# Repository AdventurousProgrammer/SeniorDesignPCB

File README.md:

# SeniorDesignPCB
This is the Diwali Light Chaser PCB For Senior Design

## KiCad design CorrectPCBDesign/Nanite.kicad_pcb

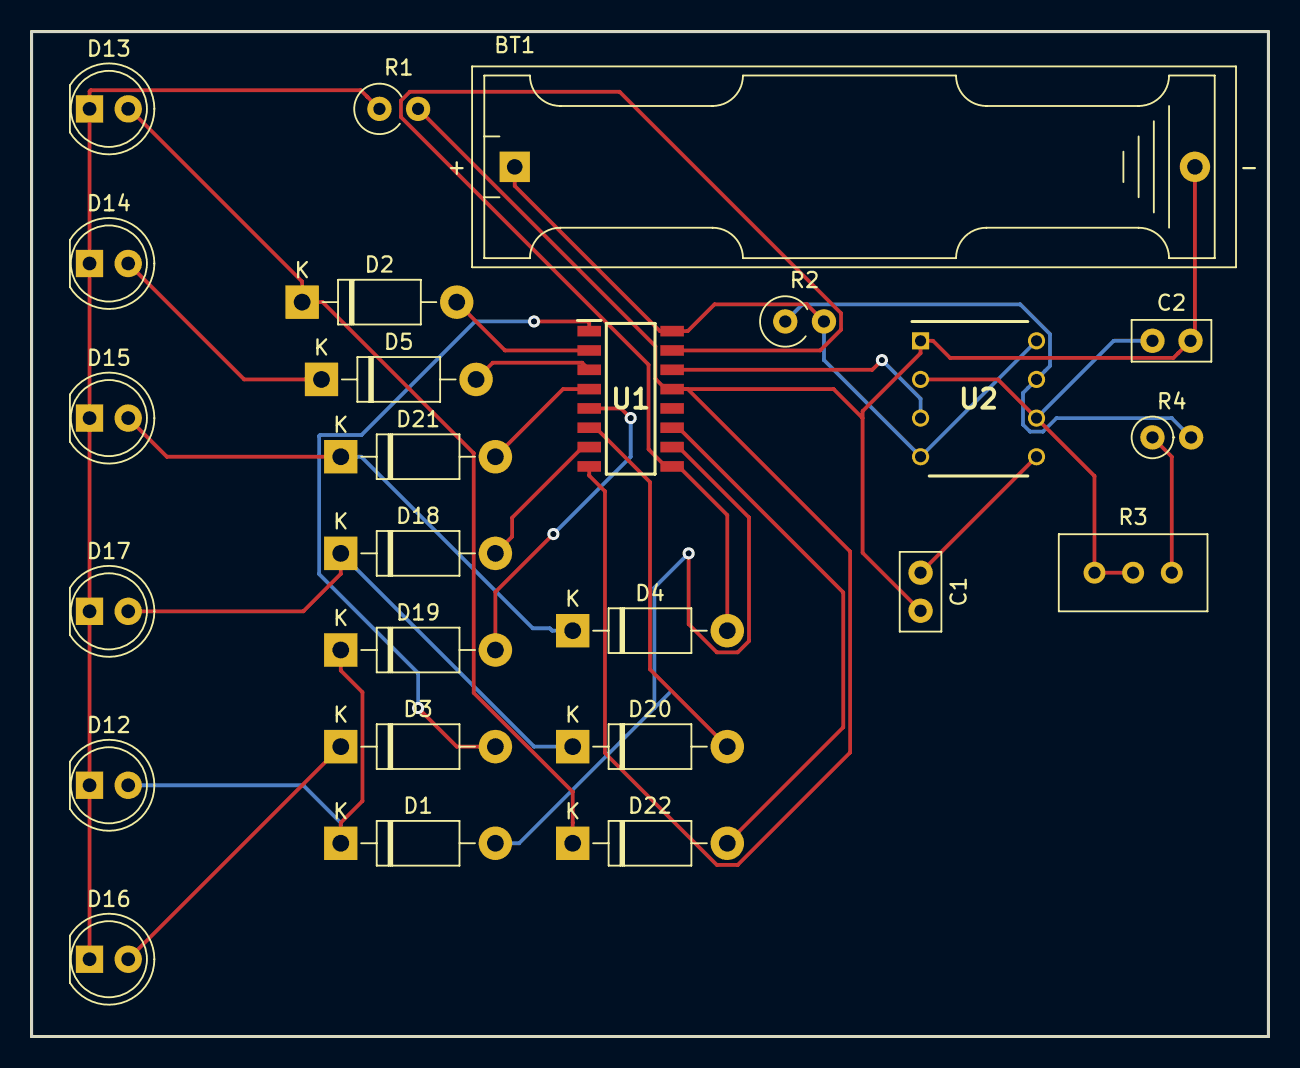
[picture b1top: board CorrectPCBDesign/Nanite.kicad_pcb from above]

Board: 2 copper layers, 81.3 x 66.0 mm, 25 parts (0 on the bottom side), 24 nets.

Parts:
BT1: Battery_Cell; BatteryHolder_Keystone_2466_1xAAA
C1: 1 nF; C_Disc_D5.0mm_W2.5mm_P2.50mm
C2: 4.7 uF; C_Disc_D5.0mm_W2.5mm_P2.50mm
D1, D2, D3, D4, D5, D18, D19, D20, D21, D22: 1N4007; D_DO-41_SOD81_P10.16mm_Horizontal
D12, D13, D14, D15, D16, D17: LED; LED_D5.0mm
R1: 1k; R_Axial_DIN0309_L9.0mm_D3.2mm_P2.54mm_Vertical
R2: 4.7k; R_Axial_DIN0309_L9.0mm_D3.2mm_P2.54mm_Vertical
R3: 1k; Potentiometer_Bourns_3296W_Vertical
R4: 100k; R_Axial_DIN0207_L6.3mm_D2.5mm_P2.54mm_Vertical
U1: 4017; SOIC127P600X175-16N
U2: TLC555; DIP762W53P254L980H533Q8N

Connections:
GNDA: BT1.2, C1.2, C2.2, R1.2, U1.8, U1.13, U2.1
unnamed: BT1.1, R2.2, U1.16, U2.4, U2.8
unnamed: C1.1, U2.5
unnamed: C2.1, R3.2, R3.3, U2.2, U2.6
unnamed: D1.1, D12.2, D19.1
unnamed: D1.2, U1.10
unnamed: D2.2, U1.2
unnamed: D3.2, U1.1
unnamed: D4.2, U1.9, U1.15
unnamed: D5.2, U1.3
unnamed: D12.1, D13.1, D14.1, D15.1, D16.1, D17.1, R1.1
unnamed: D2.1, D13.2, D22.1
unnamed: D5.1, D14.2
unnamed: D4.1, D15.2, D21.1
unnamed: D3.1, D16.2
unnamed: D17.2, D18.1, D20.1
unnamed: D18.2, U1.7
unnamed: D19.2, U1.5
unnamed: D20.2, U1.6
unnamed: D21.2, U1.4
unnamed: D22.2, U1.11
unnamed: R2.1, R4.2, U2.7
unnamed: R3.1, R4.1
unnamed: U1.14, U2.3

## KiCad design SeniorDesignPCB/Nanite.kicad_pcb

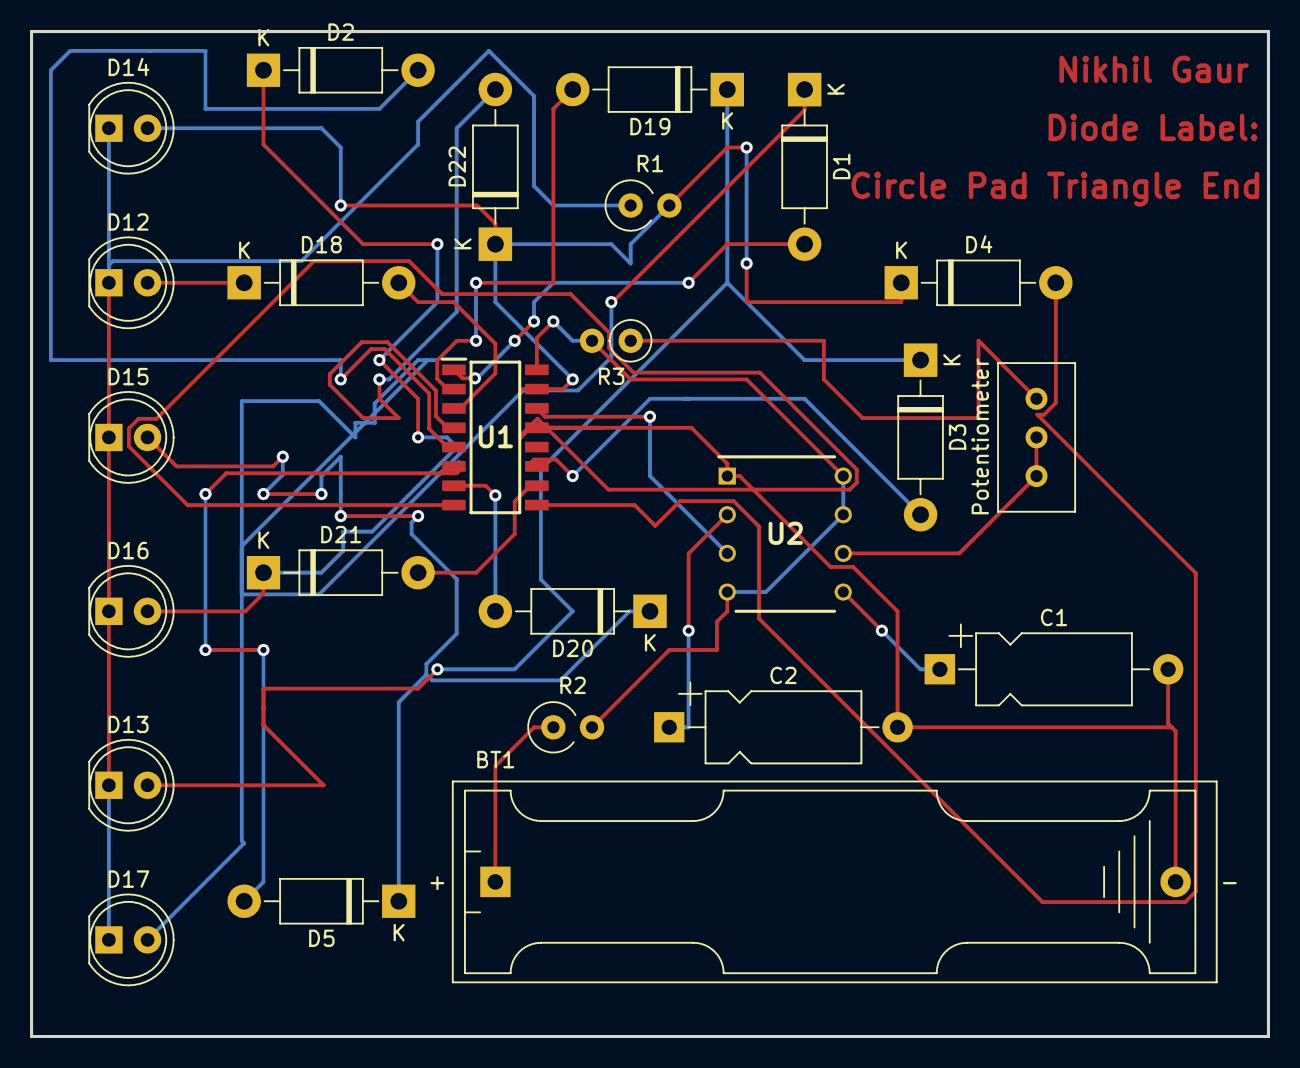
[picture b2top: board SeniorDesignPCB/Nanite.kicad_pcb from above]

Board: 2 copper layers, 81.3 x 66.0 mm, 25 parts (0 on the bottom side), 25 nets.

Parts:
BT1: Battery_Cell; BatteryHolder_Keystone_2466_1xAAA
C1: 1 nF; CP_Axial_L10.0mm_D4.5mm_P15.00mm_Horizontal
C2: 4.7 uF; CP_Axial_L10.0mm_D4.5mm_P15.00mm_Horizontal
D1, D2, D3, D4, D5, D18, D19, D20, D21, D22: DIODE; D_DO-41_SOD81_P10.16mm_Horizontal
D12, D13, D14, D15, D16, D17: LED; LED_D5.0mm
Potentiometer: 1k; Potentiometer_Bourns_3296W_Vertical
R1: 1k; R_Axial_DIN0309_L9.0mm_D3.2mm_P2.54mm_Vertical
R2: 4.7k; R_Axial_DIN0309_L9.0mm_D3.2mm_P2.54mm_Vertical
R3: 100k; R_Axial_DIN0207_L6.3mm_D2.5mm_P2.54mm_Vertical
U1: 4017; SOIC127P600X175-16N
U2: Timer_555; DIP762W53P254L980H533Q8N

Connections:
GNDA: BT1.2, C1.2, C2.2, U1.8, U1.13, U2.1
unnamed: BT1.1, R2.1
unnamed: C1.1, U2.5
unnamed: C2.1, U2.2
unnamed: D1.1, D17.2
unnamed: D1.2, U1.1
unnamed: D2.2, U1.5
unnamed: D3.2, U1.11
unnamed: D4.2, U1.9
unnamed: D5.2, U1.6
unnamed: D12.1, D13.1, D14.1, D15.1, D16.1, D17.1, R1.1
unnamed: D12.2, D18.1
unnamed: D3.1, D13.2, D19.1
unnamed: D4.1, D14.2, D22.1, R1.2, U1.15
unnamed: D5.1, D15.2, D20.1
unnamed: D2.1, D16.2, D21.1
unnamed: D18.2, U1.3
unnamed: D19.2, U1.2
unnamed: D20.2, U1.7
unnamed: D21.2, U1.10
unnamed: D22.2, U1.4
unnamed: R2.2, R3.2, U1.16, U2.4, U2.7, U2.8
unnamed: Potentiometer.1, R3.1
unnamed: Potentiometer.2, Potentiometer.3, U2.6
unnamed: U1.14, U2.3

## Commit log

2018-10-30 Working on removing intersections
2018-10-30 Finished making lines?
2018-11-04 Added all tracings
2018-11-05 one last connection new diode
2018-11-05 Fixing errors with DRC, done tracing
2018-11-05 fixing up DRC issues
2018-11-05 Done with pcb
2018-11-05 added edge cuts
2018-11-15 Correct PCB Design and Schematic
